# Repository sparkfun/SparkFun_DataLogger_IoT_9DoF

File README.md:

SparkFun DataLogger IoT – 9DoF
========================================

[*SparkFun DataLogger IoT – 9DoF (DEV-20594)*](https://www.sparkfun.com/products/20594)

An IoT-enabled ESP32-based logger with on-board IMU and magnetometer. The microSD interface is full 4-bit SDIO for fast logging.

Repository Contents
-------------------
* **/Firmware** - Example code for hardware testing
* **/Hardware** - Eagle design files (.brd, .sch)

Documentation
-------------------

* **[Hookup Guide](https://docs.sparkfun.com/SparkFun_DataLogger/)** - Basic hookup guide for the Datalogger IoT
* **[Firmware](https://github.com/sparkfun/SparkFun_DataLogger/)** - Repo for the Datalogger IoT

Product Versions
----------------

* [DEV-20594](https://www.sparkfun.com/products/20594) - v1.1 & v1.2 (minor silkscreen change)

Version History
---------------
- V1.2 - DataLogger IoT – 9DoF with minor silkscreen change
- V1.1 - Initial release, rename to DataLogger IoT – 9DoF

License Information
-------------------

This hardware and the hardware test sketches contained in this GitHub repo are _**open source**_!

Please review the LICENSE.md file for license information. 

If you have any questions or concerns on licensing, please contact technical support on our [SparkFun forums](https://forum.sparkfun.com/viewforum.php?f=152).

Distributed as-is; no warranty is given.

- Your friends at SparkFun.

_<COLLABORATION CREDIT>_

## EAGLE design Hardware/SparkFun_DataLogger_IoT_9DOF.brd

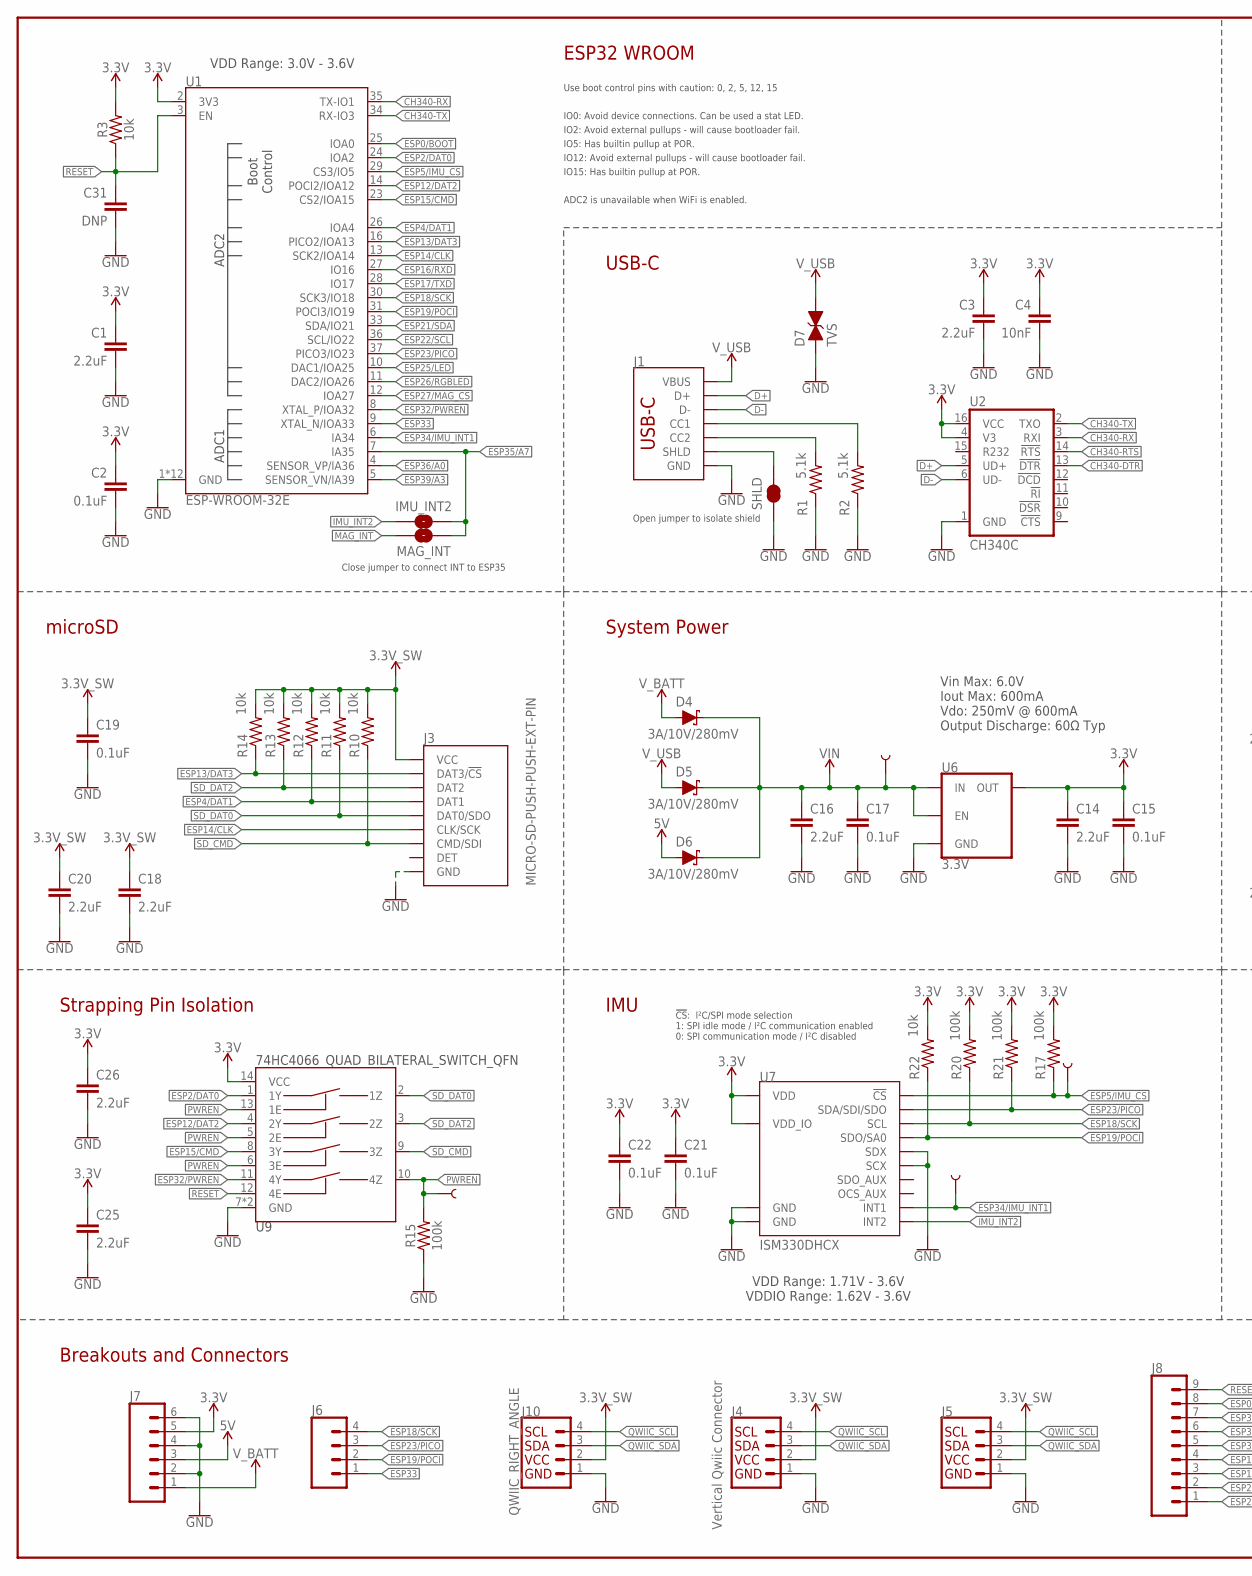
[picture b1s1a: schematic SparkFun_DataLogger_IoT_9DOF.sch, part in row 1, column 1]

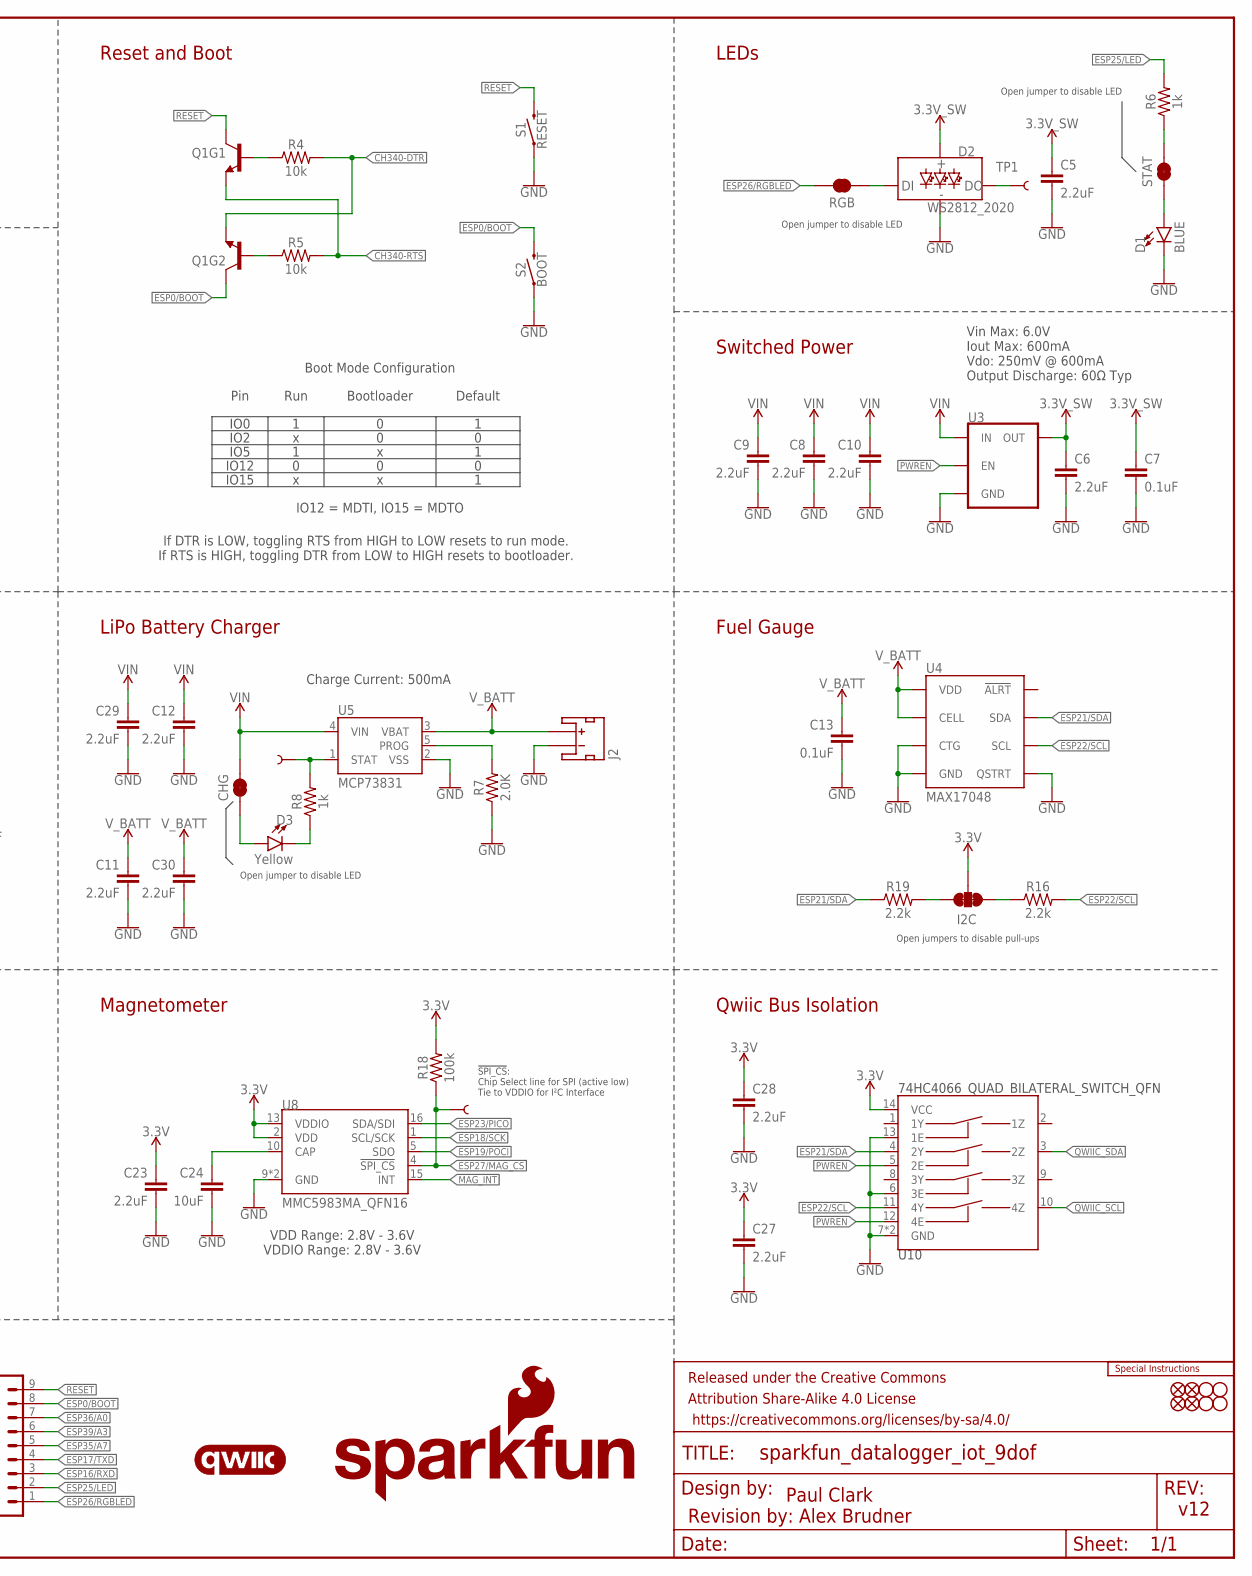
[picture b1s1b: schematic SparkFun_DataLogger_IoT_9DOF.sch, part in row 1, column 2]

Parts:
C1, C3, C5, C6, C8, C9, C10, C11, C12, C14, C16, C18, C20, C23, C25, C26, C27, C28, C29, C30: 2.2uF; 0402-TIGHT
C2, C7, C13, C15, C17, C19, C21, C22: 0.1uF; 0402-TIGHT
C4: 10nF; 0402-TIGHT
C24: 10uF; 0402-TIGHT
C31: DNP; 0402-TIGHT_NO_CREAM
CHG: JUMPER-SMT_2_NC_TRACE_SILK; SMT-JUMPER_2_NC_TRACE_SILK
D1: BLUE; LED-0603
D2: WS2812_2020; WS2812-2020
D3: Yellow; LED-0603
D4, D5, D6: 3A/10V/280mV; SOD-323
D7: TVS; 0603
FD1, FD2, FD3, FD4: FIDUCIAL1X2; FIDUCIAL-1X2
FRAME1: FRAME-LEDGER; CREATIVE_COMMONS
H1, H2, H3, H4: STAND-OFFTIGHT; STAND-OFF-TIGHT
I2C: JUMPER-SMT_3_2-NC_TRACE_SILK; SMT-JUMPER_3_2-NC_TRACE_SILK
IMU_!CS!: TEST-POINT3X5; PAD.03X.05
IMU_INT1: TEST-POINT3X5; PAD.03X.05
IMU_INT2: JUMPER-SMT_2_NO_SILK; SMT-JUMPER_2_NO_SILK
J1: USB_C_4-LAYER_PADS; USB-C-16P_4LAYER-PADS
J2: JST_2MM_MALE; JST-2-SMD
J3: MICRO-SD-PUSH-PUSH-EXT-PIN; MICROSD-EXTERNALPIN
J4: Vertical Qwiic Connector; JST04_1MM_VERT
J5: I2C_STANDARD_NO_SILK; 1X04_NO_SILK
J6: CONN_041X04_NO_SILK_NO_POP; 1X04_NO_SILK
J7: CONN_06NO_SILK_NO_POP; 1X06_NO_SILK
J8: CONN_09NO_SILK; 1X09_NO_SILK
J10: QWIIC_RIGHT_ANGLE; JST04_1MM_RA
LOGO1: SPECIAL_INSTRUCTIONS-ORDERING; ORDERING_INSTRUCTIONS
LOGO3: QWIIC_LOGO_6MM; QWIIC_6MM
LOGO5: SFE_LOGO_NAME.2_INCH; SFE_LOGO_NAME_.2
LOGO6: SFE_LOGO_FLAME.2_INCH; SFE_LOGO_FLAME_.2
MAG_!CS!: TEST-POINT3X5; PAD.03X.05
MAG_INT: JUMPER-SMT_2_NO_SILK; SMT-JUMPER_2_NO_SILK
PWREN: TEST-POINT3X5; PAD.03X.05
Q1: TRANS_NPN_DUAL-MBT3904DW1T1; SC70-6
R1, R2: 5.1k; 0402-TIGHT
R3, R4, R5, R10, R11, R12, R13, R14, R22: 10k; 0402-TIGHT
R6, R8: 1k; 0402-TIGHT
R7: 2.0K; 0402-TIGHT
R15, R17, R18, R20, R21: 100k; 0402-TIGHT
R16, R19: 2.2k; 0402-TIGHT
RGB: JUMPER-SMT_2_NC_TRACE_SILK; SMT-JUMPER_2_NC_TRACE_SILK
S1: RESET; TACTILE_SWITCH_SMD_RIGHT_ANGLE
S2: BOOT; TACTILE_SWITCH_SMD_RIGHT_ANGLE
SHLD: JUMPER-SMT_2_NC_TRACE_SILK; SMT-JUMPER_2_NC_TRACE_SILK
STAT: JUMPER-SMT_2_NC_TRACE_SILK; SMT-JUMPER_2_NC_TRACE_SILK
TP1: TEST-POINT3X5; PAD.03X.05
U1: ESP-WROOM-32E; ESP-WROOM-32D-NARROW
U2: CH340C; SO016
U3, U6: 3.3V; SOT23-5
U4: MAX17048; DFN-8
U5: MCP73831; SOT23-5
U7: ISM330DHCX; LGA-14L
U8: MMC5983MA_QFN16; LGA-16-3X3MM-4X4PINS
U9, U10: 74HC4066_QUAD_BILATERAL_SWITCH_QFN; 14-QFN
VIN, VIN1: TEST-POINT3X5; PAD.03X.05

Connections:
3.3V: C1.1, C2.1, C3.1, C4.1, C14.1, C15.1, C21.1, C22.1, C23.1, C25.1, C26.1, C27.1, C28.1, I2C.2, J7.5, R3.2, R17.2, R18.2, R20.2, R21.2, R22.2, U1.2 (3V3), U2.4 (V3), U2.16 (VCC), U6.5 (OUT), U7.P5 (VDD_IO), U7.P8 (VDD), U8.2 (VDD), U8.13 (VDDIO), U9.14 (VCC), U10.14 (VCC)
3.3V_SW: C5.1, C6.1, C7.1, C18.1, C19.1, C20.1, D2.VCC, J3.4 (VCC), J4.2, J5.2, J10.2, R10.2, R11.2, R12.2, R13.2, R14.2, U3.5 (OUT)
5V: D6.A, J7.3
!RESET!: C31.1, J8.9, Q1.3 (C), R3.1, S1.2, U1.3 (EN), U9.12 (4E)
CAP: C24.1, U8.10 (CAP)
CH340-DTR: Q1.1 (E), R4.2, U2.13 (!DTR)
CH340-RTS: Q1.4 (E), R5.2, U2.14 (!RTS)
CH340-RX: U1.35 (TX-IO1), U2.3 (RXI)
CH340-TX: U1.34 (RX-IO3), U2.2 (TXO)
D+: J1.A6 (D+), J1.B6 (D+), U2.5 (UD+)
D-: J1.A7 (D-), J1.B7 (D-), U2.6 (UD-)
ESP0/!BOOT!: J8.8, Q1.6 (C), S2.2, U1.25 (IOA0)
ESP2/DAT0: U1.24 (IOA2), U9.1 (1Y)
ESP4/DAT1: J3.8 (DAT1), R12.1, U1.26 (IOA4)
ESP5/!IMU_CS!: IMU_!CS!.1, R17.1, U1.29 (CS3/IO5), U7.P12 (!CS!)
ESP12/DAT2: U1.14 (POCI2/IOA12), U9.4 (2Y)
ESP13/DAT3: J3.2 (DAT3/!CS!), R14.1, U1.16 (PICO2/IOA13)
ESP14/CLK: J3.5 (CLK/SCK), U1.13 (SCK2/IOA14)
ESP15/CMD: U1.23 (CS2/IOA15), U9.8 (3Y)
ESP16/RXD: J8.3, U1.27 (IO16)
ESP17/TXD: J8.4, U1.28 (IO17)
ESP18/SCK: J6.4, R20.1, U1.30 (SCK3/IO18), U7.P13 (SCL), U8.1 (SCL/SCK)
ESP19/POCI: J6.2, R22.1, U1.31 (POCI3/IO19), U7.P1 (SDO/SA0), U8.5 (SDO)
ESP21/SDA: R19.1, U1.33 (SDA/IO21), U4.8 (SDA), U10.4 (2Y)
ESP22/SCL: R16.2, U1.36 (SCL/IO22), U4.7 (SCL), U10.11 (4Y)
ESP23/PICO: J6.3, R21.1, U1.37 (PICO3/IO23), U7.P14 (SDA/SDI/SDO), U8.16 (SDA/SDI)
ESP25/LED: J8.2, R6.2, U1.10 (DAC1/IOA25)
ESP26/RGBLED: J8.1, RGB.2, U1.11 (DAC2/IOA26)
ESP27/!MAG_CS!: MAG_!CS!.1, R18.1, U1.12 (IOA27), U8.4 (!SPI_CS!)
ESP32/PWREN: U1.8 (XTAL_P/IOA32), U9.11 (4Y)
ESP33: J6.1, U1.9 (XTAL_N/IOA33)
ESP34/IMU_INT1: IMU_INT1.1, U1.6 (IA34), U7.P4 (INT1)
ESP35/A7: IMU_INT2.2, J8.5, MAG_INT.2, U1.7 (IA35)
ESP36/A0: J8.7, U1.4 (SENSOR_VP/IA36)
ESP39/A3: J8.6, U1.5 (SENSOR_VN/IA39)
GND: C1.2, C2.2, C3.2, C4.2, C5.2, C6.2, C7.2, C8.2, C9.2, C10.2, C11.2, C12.2, C13.2, C14.2, C15.2, C16.2, C17.2, C18.2, C19.2, C20.2, C21.2, C22.2, C23.2, C24.2, C25.2, C26.2, C27.2, C28.2, C29.2, C30.2, C31.2, D1.C, D2.GND, D7.1 (A), J1.GND, J1.GND2 (GND), J2.1 (-), J3.6 (GND), J3.10 (GND), J3.11 (GND), J3.12 (GND), J3.13 (GND), J4.1, J5.1, J7.2, J7.4, J7.6, J10.1, R1.1, R2.1, R7.1, R15.1, S1.1, S2.1, SHLD.1, U1.1 (GND), U1.15 (GND), U1.38 (GND), U1.GND1 (GND), U1.GNDT1 (GND), U1.GNDT2 (GND), U1.GNDT3 (GND), U1.GNDT4 (GND), U1.GNDT5 (GND), U1.GNDT6 (GND), U1.GNDT7 (GND), U1.GNDT8 (GND), U2.1 (GND), U3.2 (GND), U4.1 (CTG), U4.4 (GND), U4.6 (QSTRT), U4.9 (GND), U5.2 (VSS), U6.2 (GND), U7.P2 (SDX), U7.P3 (SCX), U7.P6 (GND), U7.P7 (GND), U8.9 (GND), U8.11 (GND), U9.7 (GND), U9.EPAD (GND), U10.6 (3E), U10.7 (GND), U10.13 (1E), U10.EPAD (GND)
IMU_INT2: IMU_INT2.1, U7.P9 (INT2)
MAG_INT: MAG_INT.1, U8.15 (INT)
unnamed: J1.B5 (CC2), R1.2
unnamed: J1.A5 (CC1), R2.2
unnamed: Q1.2 (B), R5.1
unnamed: Q1.5 (B), R4.1
unnamed: R6.1, STAT.2
unnamed: D2.DO, TP1.1
unnamed: CHG.1, D3.A
unnamed: D3.C, R8.1
unnamed: R8.2, U5.1 (STAT), VIN1.1
unnamed: R7.2, U5.5 (PROG)
unnamed: D2.DI, RGB.1
unnamed: D1.A, STAT.1
unnamed: I2C.1, R16.1
unnamed: I2C.3, R19.2
PWREN: PWREN.1, R15.2, U3.3 (EN), U9.5 (2E), U9.6 (3E), U9.10 (4Z), U9.13 (1E), U10.5 (2E), U10.12 (4E)
QWIIC_SCL: J4.4, J5.4, J10.4, U10.10 (4Z)
QWIIC_SDA: J4.3, J5.3, J10.3, U10.3 (2Z)
SD_CMD: J3.3 (CMD/SDI), R10.1, U9.9 (3Z)
SD_DAT0: J3.7 (DAT0/SDO), R11.1, U9.2 (1Z)
SD_DAT2: J3.1 (DAT2), R13.1, U9.3 (2Z)
SHIELD: J1.SHLD1 (SHLD), J1.SHLD2 (SHLD), J1.SHLD3 (SHLD), J1.SHLD4 (SHLD), SHLD.2
VIN: C8.1, C9.1, C10.1, C12.1, C16.1, C17.1, C29.1, CHG.2, D4.C, D5.C, D6.C, U3.1 (IN), U5.4 (VIN), U6.1 (IN), U6.3 (EN), VIN.1
V_BATT: C11.1, C13.1, C30.1, D4.A, J2.2 (+), J7.1, U4.2 (CELL), U4.3 (VDD), U5.3 (VBAT)
V_USB: D5.A, D7.2 (C), J1.VBUS1 (VBUS), J1.VBUS2 (VBUS)

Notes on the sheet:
ESP32 WROOM
USB-C
Paul Clark
v12
Reset and Boot
LEDs
Switched Power
Fuel Gauge
LiPo Battery Charger
System Power
microSD
Strapping Pin Isolation
IMU
VDD Range: 1.71V - 3.6V VDDIO Range: 1.62V - 3.6V
VDD Range: 2.8V - 3.6V VDDIO Range: 2.8V - 3.6V
Magnetometer
Qwiic Bus Isolation
Breakouts and Connectors
Charge Current: 500mA
VDD Range: 3.0V - 3.6V
Vin Max: 6.0V Iout Max: 600mA Vdo: 250mV @ 600mA Output Discharge: 60Ω Typ
If DTR is LOW, toggling RTS from HIGH to LOW resets to run mode. If RTS is HIGH, toggling DTR from LOW to HIGH resets to bootloader.
Pin
IO0
IO2
IO12
IO15
IO5
Run
Bootloader
Default
IO12 = MDTI, IO15 = MDTO
Boot Mode Configuration
IO0: Avoid device connections. Can be used a stat LED.
ADC2 is unavailable when WiFi is enabled.
IO12: Avoid external pullups - will cause bootloader fail.
Use boot control pins with caution: 0, 2, 5, 12, 15
IO2: Avoid external pullups - will cause bootloader fail.
IO15: Has builtin pullup at POR.
IO5: Has builtin pullup at POR.

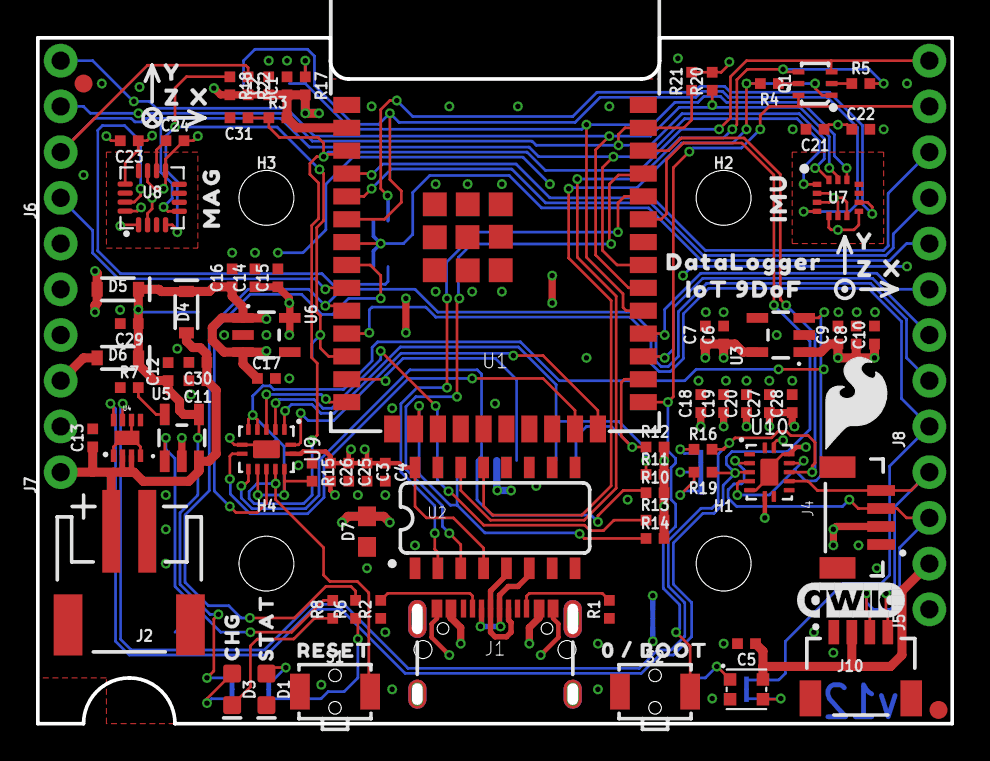
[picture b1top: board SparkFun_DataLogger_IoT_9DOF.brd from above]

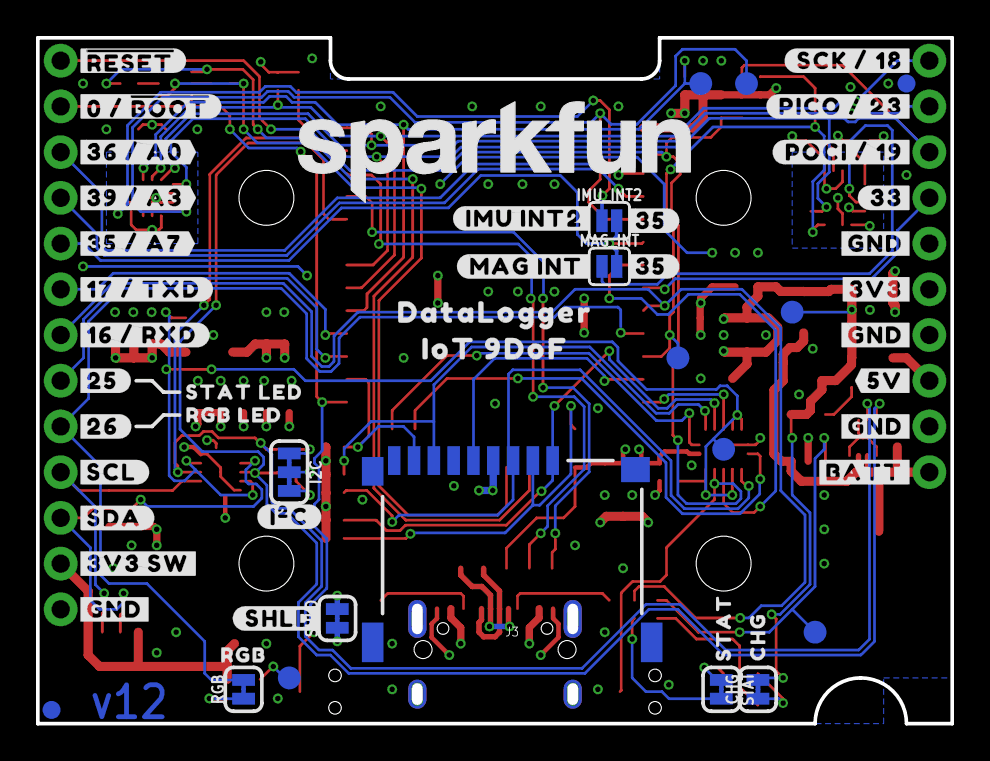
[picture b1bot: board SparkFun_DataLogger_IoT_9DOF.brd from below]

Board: 4 copper layers, 50.8 x 38.1 mm, 158 parts (54 on the bottom side), 62 nets.

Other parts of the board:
U$1: IOT_9DOF0
U$2: RESET0
U$3, U$6: STAT0
U$4, U$5: CHG0
U$7: 0_#_BOOT0
U$8: IMU0
U$9: MAG0
U$10, U$13: X0
U$11, U$14: Y0
U$12, U$15: Z0
U$16: ##RESET##0
U$17: #0_#_#BOOT##0
U$18: #36_#_A0#0
U$19: #39_#_A3#0
U$20: #35_#_A7#0
U$21: #17_#_TXD#0
U$22: #16_#_RXD#0
U$23: #25#0
U$24: #26#0
U$25: #SCL#0
U$26: #SDA#0
U$27: #3V3_SW#0
U$28: #GND#0
U$29, U$30, U$31: #GND#1
U$32: #BATT#0
U$33: #5V#0
U$34: #3V3#0
U$35: #33#0
U$36: #POCI_#_19#0
U$37: #PICO_#_23#0
U$38: #SCK_#_18#0
U$40: #IMU_INT2#0
U$41: #MAG_INT#0
U$42, U$43: #35#0
U$44: IOT_9DOF10
U$45: #SHLD#0
U$46: #I�C#0
U$47: STAT_LED0
U$48: RGB_LED0
U$49: RGB0
U$50: DATALOGGER0
U$51: DATALOGGER1

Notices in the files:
parts and their libraries:
SparkFun-Capacitors: Licensing: Creative Commons ShareAlike 4.0 International - https://creativecommons.org/licenses/by-sa/4.0
SparkFun-Aesthetics: Released under the Creative Commons Attribution Share-Alike 4.0 License
SparkFun-Aesthetics: https://creativecommons.org/licenses/by-sa/4.0
